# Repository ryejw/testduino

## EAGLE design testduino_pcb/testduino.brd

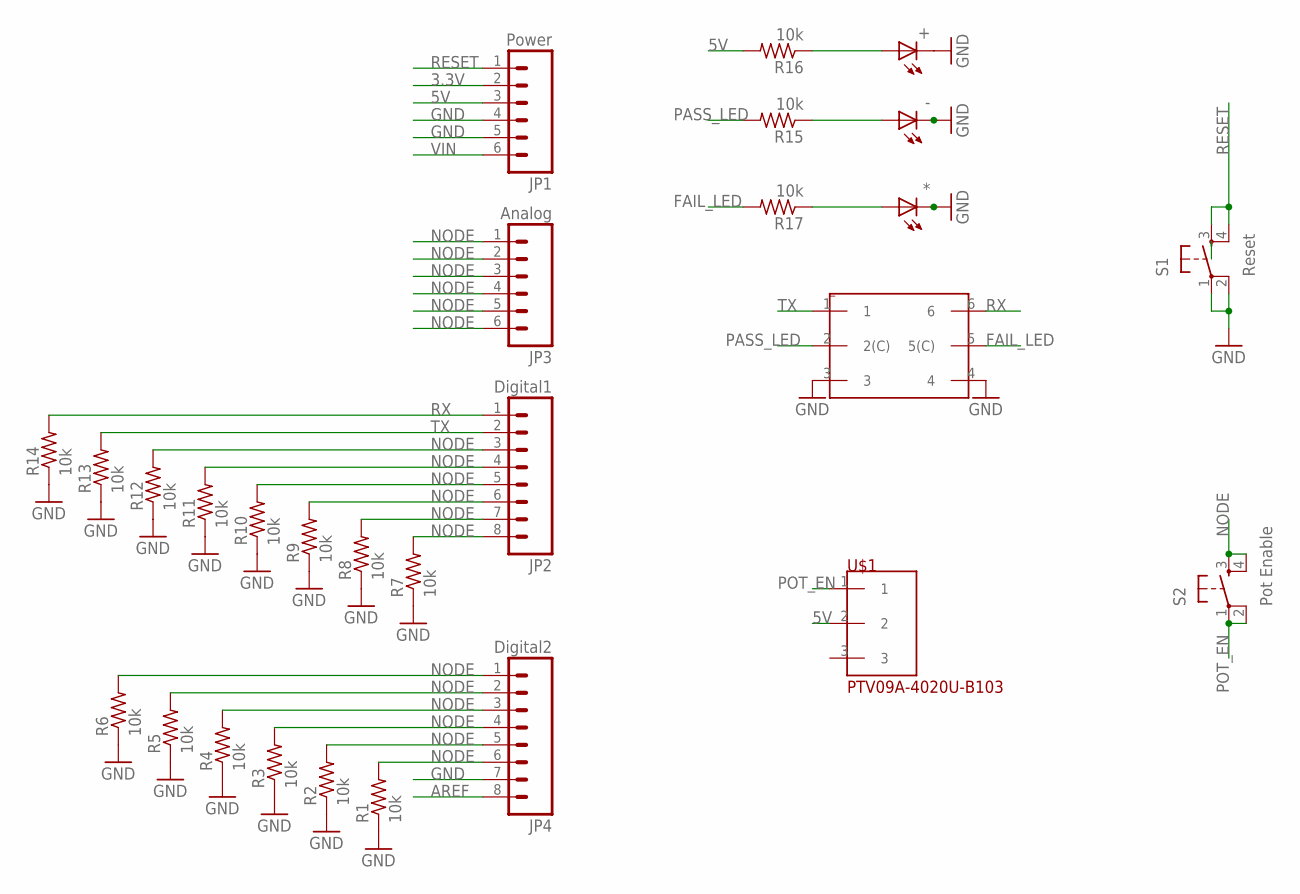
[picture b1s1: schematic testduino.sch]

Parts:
*: LEDSML0805; SML0805
+: LEDSML0805; SML0805
-: LEDSML0805; SML0805
JP1: Power; 1X06
JP2: Digital1; 1X08
JP3: Analog; 1X06
JP4: Digital2; 1X08
R1, R2, R3, R4, R5, R6, R7, R8, R9, R10, R11, R12, R13, R14, R15, R16, R17: 10k; R0402
S1: Reset; TACTILE-PTH
S2: Pot Enable; TACTILE-PTH
U$1: PTV09A-4020U-B103; PTV09A-1
_: JS202011SCQN

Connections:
3.3V: JP1.2
5V: JP1.3, R16.2, U$1.2
AREF: JP4.8
FAIL_LED: R17.2, _.5 (5(C))
GND: *.C, +.C, -.C, JP1.4, JP1.5, JP4.7, R1.1, R2.1, R3.1, R4.1, R5.1, R6.1, R7.1, R8.1, R9.1, R10.1, R11.1, R12.1, R13.1, R14.1, S1.1, S1.2, _.3, _.4
unnamed: -.A, R15.1
unnamed: +.A, R16.1
unnamed: *.A, R17.1
NODE: JP2.3, JP2.4, JP2.5, JP2.6, JP2.7, JP2.8, JP3.1, JP3.2, JP3.3, JP3.4, JP3.5, JP3.6, JP4.1, JP4.2, JP4.3, JP4.4, JP4.5, JP4.6, R1.2, R2.2, R3.2, R4.2, R5.2, R6.2, R7.2, R8.2, R9.2, R10.2, R11.2, R12.2, S2.3, S2.4
PASS_LED: R15.2, _.2 (2(C))
POT_EN: S2.1, S2.2, U$1.1
RESET: JP1.1, S1.3, S1.4
RX: JP2.1, R14.2, _.6
TX: JP2.2, R13.2, _.1
VIN: JP1.6

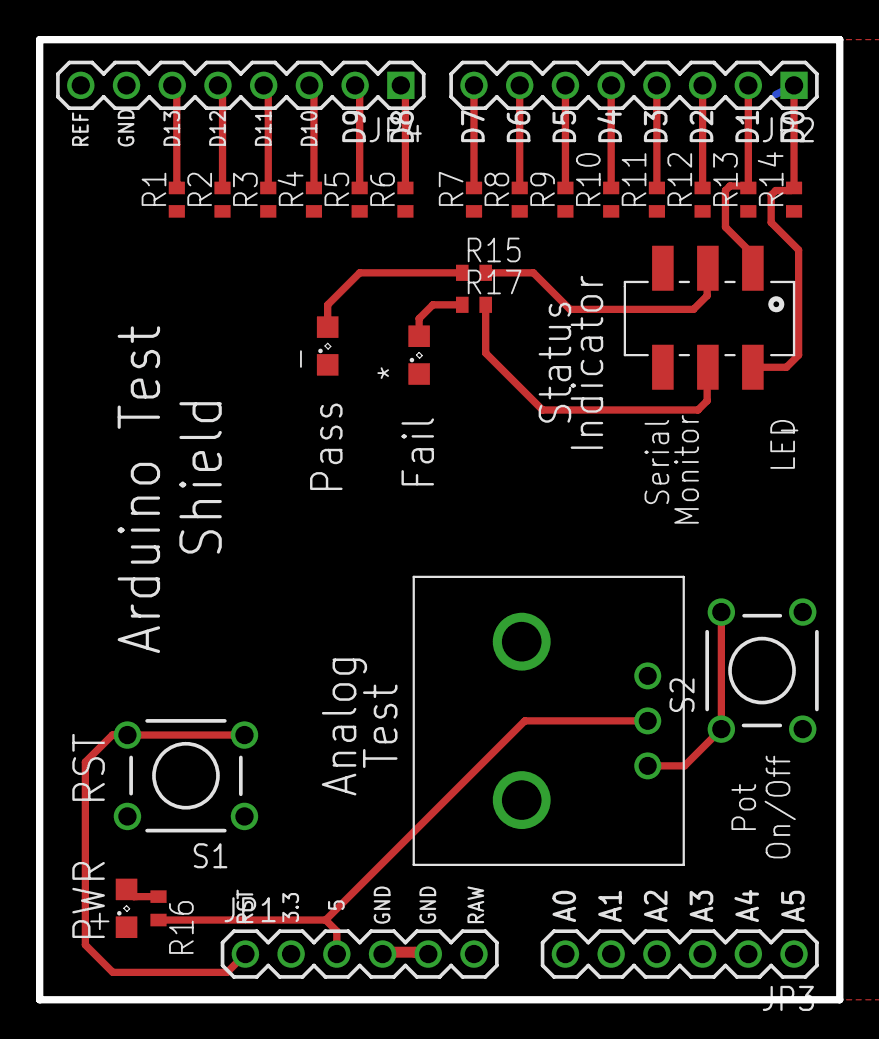
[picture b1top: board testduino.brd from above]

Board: 2 copper layers, 44.5 x 53.3 mm, 28 parts (0 on the bottom side), 12 nets.

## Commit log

2014-07-03 init
